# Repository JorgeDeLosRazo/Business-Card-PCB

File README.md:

# Business Card PCB
This repo includes the KiCad files for a PCB I designed that will function as a business card. The hardware on top of the PCB will allow the user
to play a simple "Simon Says" style of game, where LEDs will display a pattern of lights that the user will have to replicate by pressing three tactile buttons.

## KiCad

## Components

| Component       | Qty. |
|-----------------|------|
| ATtiny85        | 1    | 
| Tactile Buttons | 4    |
| Piezo Buzzer    | 1    |
| Red LED         | 3    |
| Yellow LEDs     | 1    |
| Green LED       | 1    |

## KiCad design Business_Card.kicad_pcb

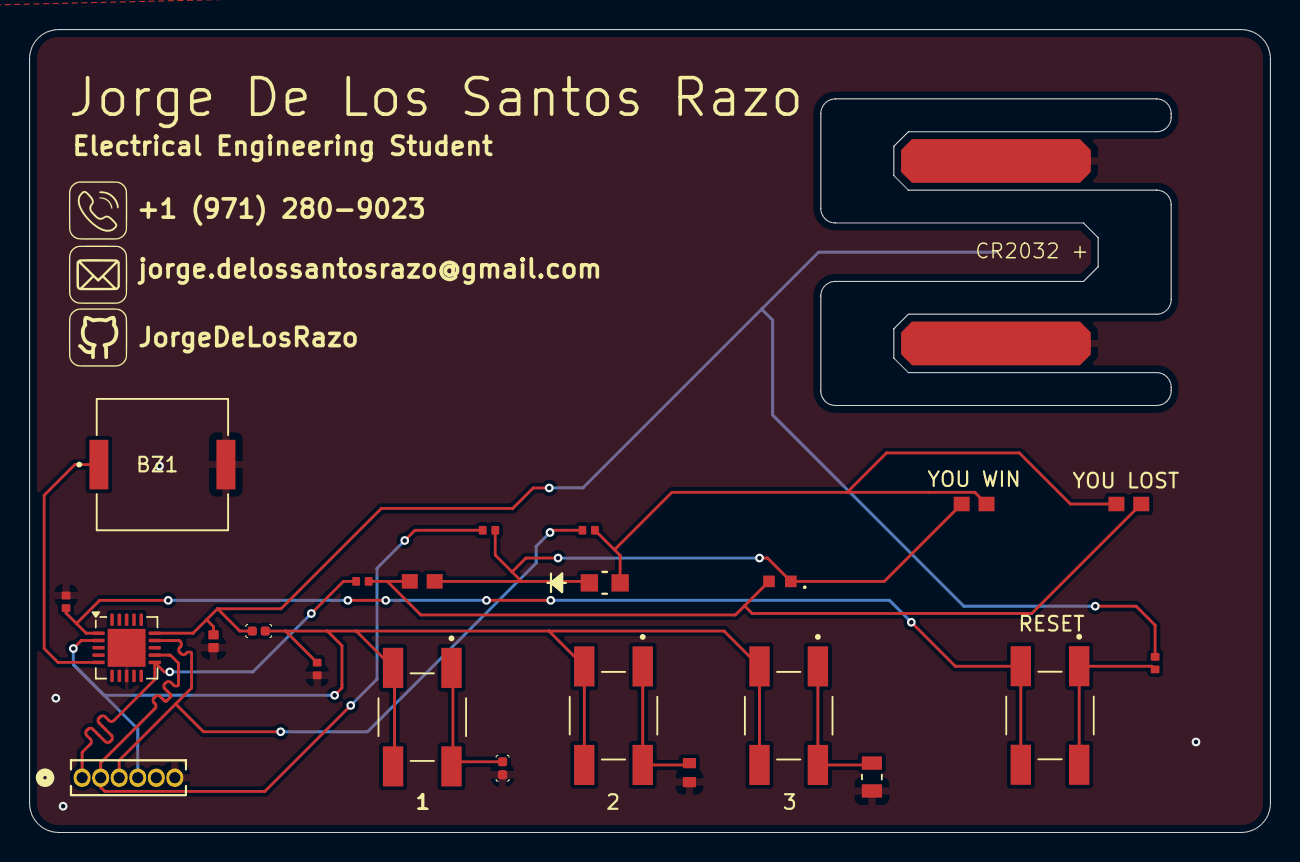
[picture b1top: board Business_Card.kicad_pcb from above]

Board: 2 copper layers, 85.0 x 55.0 mm, 24 parts (0 on the bottom side), 15 nets.

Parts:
1, 2, 3: B3SN-3012P; SW_B3SN-3012P
BT1: Battery_Cell; Coin_Battery_Holder_CR2032
BZ1: Buzzer; piezo_buzzer
C1: 10uF; C_106
C2: 0.1uF; C_104
J2: Conn_01x06; conn_01x06
LED1: RED_LED; SMD_RED_LTST-S270KRKT
LED2: GREEN_LED; SMD__GREEN_LTST-C170GKT_LTO
LED3: YELLOW_LED; YELLOW_LED_.LTST-C190KSKT
LED4: WON_LED; SMD_RED_LTST-S270KRKT
LED5: LOST_LED; SMD_RED_LTST-S270KRKT
R1, R2, R3, R8: 220Ω; 221_R_RESC1005X40N
R4, R5: 10k; R_0103
R6: 4.7k; R_0472
R7: 2.2k; R_0222
R9: 220; 221_R_RESC1005X40N
RESET: B3SN-3012P; SW_B3SN-3012P
U1: ATtiny85-20M; QFN-20-1EP_4x4mm_P0.5mm_EP2.6x2.6mm

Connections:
+3V0: BT1.1 (+), C1.1, R4.1, R8.1, U1.15 (VCC)
/PB0: J2.1, R1.1, U1.11 (AREF/PB0)
/PB1: J2.2, R2.1, U1.12 (PB1)
/PB2: J2.3, R3.1, U1.14 (PB2)
/PB3: 1.3, 1.4, 2.3, 2.4, 3.3, 3.4, C2.1, J2.4, R4.2, U1.2 (XTAL1/PB3)
/PB4: BZ1.1 (+), U1.5 (XTAL2/PB4)
/RESET: R9.1, RESET.3, RESET.4, U1.1 (~RESET/PB5)
GND: BT1.2 (-), BZ1.2 (-), C1.2, C2.2, J2.6, R5.1, R6.1, R7.1, R9.2, U1.8 (GND), U1.21 (GND)
unnamed: LED1.2 (A), LED2.1 (K), LED3.1 (K), LED4.2 (A), R2.2
unnamed: LED1.1 (K), LED3.2 (A), LED5.2 (A), R1.2
unnamed: LED2.2 (A), LED4.1 (K), LED5.1 (K), R3.2
unnamed: 1.1, 1.2, R5.2
unnamed: 2.1, 2.2, R6.2
unnamed: 3.1, 3.2, R7.2
unnamed: R8.2, RESET.1, RESET.2

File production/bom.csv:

Designator,Footprint,Quantity,Value,LCSC Part #
"1, 2, 3, RESET",SW_B3SN-3012P,4,B3SN-3012P,
BT1,Coin_Battery_Holder_CR2032,1,Battery_Cell,
BZ1,piezo_buzzer,1,Buzzer,
C1,C_106,1,10uF,
C2,C_104,1,0.1uF,
J2,conn_01x06,1,Conn_01x06,
LED1,SMD_RED_LTST-S270KRKT,1,RED_LED,
LED2,SMD__GREEN_LTST-C170GKT_LTO,1,GREEN_LED,
LED3,YELLOW_LED_.LTST-C190KSKT,1,YELLOW_LED,
LED4,SMD_RED_LTST-S270KRKT,1,WON_LED,
LED5,SMD_RED_LTST-S270KRKT,1,LOST_LED,
"R1, R2, R3, R8",221_R_RESC1005X40N,4,220Ω,
"R4, R5",R_0103,2,10k,
R6,R_0472,1,4.7k,
R7,R_0222,1,2.2k,
R9,221_R_RESC1005X40N,1,220,
U1,QFN-20-1EP_4x4mm_P0.5mm_EP2.6x2.6mm,1,ATtiny85-20M,

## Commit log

2025-09-22 created .gitignore file
2025-09-25 updated schematic
2025-09-25 nothing new
2025-09-28 added code for buttons
2025-09-28 reorginized repo
2025-10-28 updated schemaatics
2025-11-25 extra stuff
2025-12-29 Finished PCB
2025-12-31 cleared all the DRC errors
2026-02-17 created symbol folder
